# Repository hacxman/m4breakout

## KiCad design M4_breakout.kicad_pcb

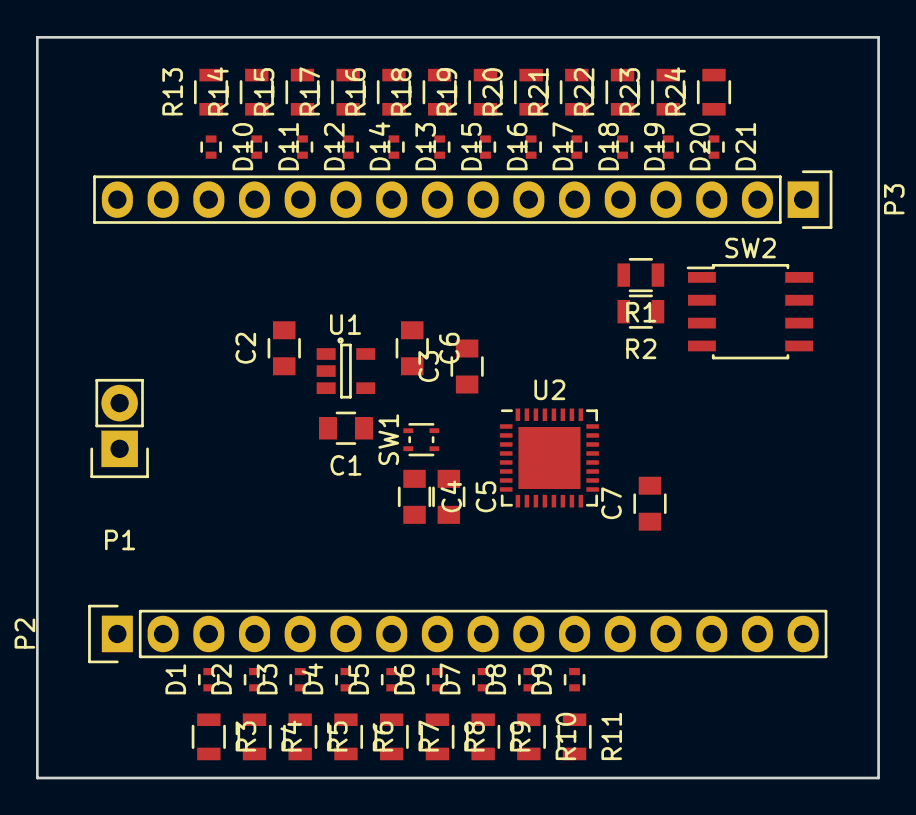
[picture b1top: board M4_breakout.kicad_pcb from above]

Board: 2 copper layers, 46.7 x 41.1 mm, 58 parts (0 on the bottom side), 50 nets, no tracks yet.

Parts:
C1, C5: 10n; C_0805
C2, C4: 1u; C_0805
C3, C7: 100n; C_0805
C6: 2u2; C_0805
D1, D2, D3, D4, D5, D6, D7, D8, D9, D10, D11, D12, D13, D14, D15, D16, D17, D18, D19, D20, D21: Led_Small; R_0402
P1: CONN_01X02; Pin_Header_Straight_1x02
P2, P3: CONN_01X16; Pin_Header_Straight_1x16
R1, R2: 100k; R_0805
R3, R4, R5, R6, R7, R8, R9, R10, R11, R13, R14, R15, R16, R17, R18, R19, R20, R21, R22, R23, R24: 10R; R_0805
SW1: SPST; SOT-543
SW2: QDIPSW; SOIC-8_3.9x4.9mm_Pitch1.27mm
U1: LP2985LV; SOT-23-5
U2: STM32F318K8; QFN-32-1EP_5x5mm_Pitch0.5mm

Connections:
GND: C1.2, C2.1, C3.2, C4.2, C5.2, C6.1, C7.1, P1.1, P2.1, R2.2, SW1.1, SW2.3, U1.2, U2.6, U2.16, U2.31, U2.32
unnamed: C1.1, U1.4
unnamed: D1.1, R3.1
unnamed: D1.2, P2.3, U2.7
unnamed: D2.1, R4.1
unnamed: D2.2, P2.4, U2.8
unnamed: D3.1, R5.1
unnamed: D3.2, P2.5, U2.9
unnamed: D4.1, R6.1
unnamed: D4.2, P2.6, U2.10
unnamed: D5.1, R7.1
unnamed: D5.2, P2.7, U2.11
unnamed: D6.1, R8.1
unnamed: D6.2, P2.8, U2.12
unnamed: D7.1, R9.1
unnamed: D7.2, P2.9, U2.13
unnamed: D8.1, R10.1
unnamed: D8.2, P2.10, U2.14
unnamed: D9.1, R11.1
unnamed: D9.2, P2.11, U2.15
unnamed: D10.1, R13.1
unnamed: D10.2, P3.14, U2.29
unnamed: D11.1, R14.1
unnamed: D11.2, P3.13, U2.28
unnamed: D12.1, R15.1
unnamed: D12.2, P3.12, U2.27
unnamed: D13.1, R16.1
unnamed: D13.2, P3.10, U2.25
unnamed: D14.1, R17.1
unnamed: D14.2, P3.11, U2.26
unnamed: D15.1, R18.1
unnamed: D15.2, P3.9, U2.24
unnamed: D16.1, R19.1
unnamed: D16.2, P3.8, U2.23
unnamed: D17.1, R20.1
unnamed: D17.2, P3.7, U2.22
unnamed: D18.1, R21.1
unnamed: D18.2, P3.6, U2.21
unnamed: D19.1, R22.1
unnamed: D19.2, P3.5, U2.20
unnamed: D20.1, R23.1
unnamed: D20.2, P3.4, U2.19
unnamed: D21.1, R24.1
unnamed: D21.2, P3.3, U2.18
unnamed: P2.2, SW1.2, SW2.7, SW2.8, U2.4
unnamed: R1.1, SW2.1
unnamed: R2.1, SW2.2
unnamed: R3.2, R4.2, R5.2, R6.2, R7.2, R8.2, R9.2, R10.2, R11.2, R13.2, R14.2, R15.2, R16.2, R17.2, R18.2, R19.2, R20.2, R21.2, R22.2, R23.2, R24.2, SW2.6
VCC: C2.2, C3.1, P1.2, U1.1, U1.3, U2.1
VDD: C4.1, C5.1, C6.2, C7.2, P3.16, R1.2, U1.5, U2.5, U2.17

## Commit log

2016-08-28 proper reset
